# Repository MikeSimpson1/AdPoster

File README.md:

[![Contributors][contributors-shield]][contributors-url]
[![Forks][forks-shield]][forks-url]
[![Stargazers][stars-shield]][stars-url]
[![Issues][issues-shield]][issues-url]
[![LinkedIn][linkedin-shield]][linkedin-url]

<!-- PROJECT LOGO -->
<br />
<div align="center">

  <h3 align="center">Marketplace Ad Poster</h3>

  <p align="center">
    <br />
    <a href="https://github.com/MikeSimpson1/AdPoster"><strong>Explore the docs »</strong></a>
    <br />
    <br />
    <a href="https://github.com/MikeSimpson1/AdPoster">View Demo</a>
    ·
    <a href="https://github.com/MikeSimpson1/AdPoster/issues">Report Bug</a>
    ·
    <a href="https://github.com/MikeSimpson1/AdPoster/issues">Request Feature</a>
  </p>
</div>

<!-- TABLE OF CONTENTS -->
<details>
  <summary>Table of Contents</summary>
  <ol>
    <li>
      <a href="#about-the-project">About The Project</a>
      <ul>
        <li><a href="#built-with">Built With</a></li>
      </ul>
    </li>
  </ol>
</details>

<!-- ABOUT THE PROJECT -->
## About The Project

[![Product Name Screen Shot][product-screenshot]](https://example.com)

Lorem ipsum

<p align="right">(<a href="#readme-top">back to top</a>)</p>

### Built With

* [![Python][Python]][Python-url]
* [![Selenium][Selenium]][Selenium-url]
* [![OpenCV][OpenCV]][OpenCV-url]

<p align="right">(<a href="#readme-top">back to top</a>)</p>

<!-- MARKDOWN LINKS & IMAGES -->
[contributors-shield]: https://img.shields.io/github/contributors/MikeSimpson1/AdPoster.svg?style=for-the-badge
[contributors-url]: https://github.com/MikeSimpson1/AdPoster/graphs/contributors
[forks-shield]: https://img.shields.io/github/forks/MikeSimpson1/AdPoster.svg?style=for-the-badge
[forks-url]: https://github.com/MikeSimpson1/AdPoster/network/members
[stars-shield]: https://img.shields.io/github/stars/MikeSimpson1/AdPoster.svg?style=for-the-badge
[stars-url]: https://github.com/MikeSimpson1/AdPoster/stargazers
[issues-shield]: https://img.shields.io/github/issues/MikeSimpson1/AdPoster.svg?style=for-the-badge
[issues-url]: https://github.com/MikeSimpson1/AdPoster/issues
[license-shield]: https://img.shields.io/github/license/MikeSimpson1/AdPoster.svg?style=for-the-badge
[license-url]: https://github.com/MikeSimpson1/AdPoster/blob/master/LICENSE.txt
[linkedin-shield]: https://img.shields.io/badge/-LinkedIn-black.svg?style=for-the-badge&logo=linkedin&colorB=555
[linkedin-url]: https://linkedin.com/in/mike-simpson-86237419a/
[product-screenshot]: ProductImages/Uncased_device.jpg
[Selenium]: https://img.shields.io/pypi/pyversions/Selenium?logo=Selenium
[Selenium-url]: https://www.selenium.dev/
[Python]: https://img.shields.io/pypi/pyversions/pybadges.svg
[Python-url]: https://www.python.org/
[OpenCV]: https://img.shields.io/pypi/pyversions/Opencv-python?logo=OpenCV
[OpenCV-url]: https://pypi.org/project/opencv-python/

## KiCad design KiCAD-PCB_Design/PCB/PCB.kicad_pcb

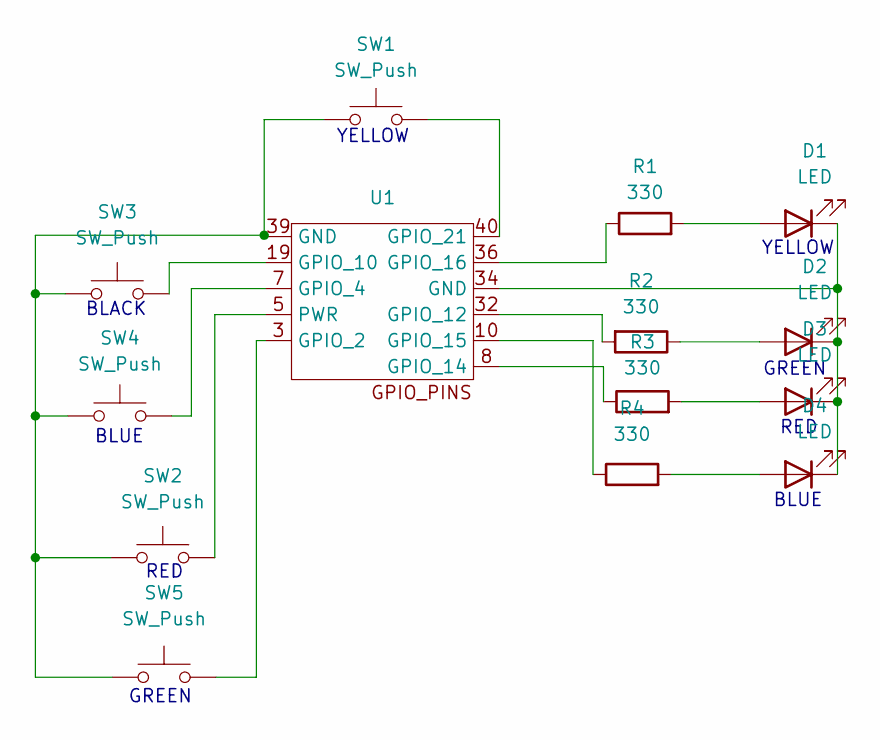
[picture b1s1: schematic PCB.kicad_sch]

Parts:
D1, D2, D3, D4: LED; LED_D5.0mm
R1, R2, R3, R4: 330; R_0201_0603Metric
SW1, SW2, SW3, SW4, SW5: SW_Push; SW_PUSH-12mm
U1: GPIO_PINS_TEST

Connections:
unnamed: D1.2 (A), R1.2
unnamed: D1.1 (K), D2.1 (K), D3.1 (K), D4.1 (K), U1.34 (GND)
unnamed: D2.2 (A), R2.1
unnamed: D3.2 (A), R3.2
unnamed: D4.2 (A), R4.2
unnamed: SW1.1, SW2.1, SW3.1, SW4.1, SW5.1, U1.39 (GND)
unnamed: SW5.2, U1.3 (GPIO_2)
unnamed: SW4.2, U1.7 (GPIO_4)
unnamed: SW3.2, U1.19 (GPIO_10)
unnamed: R2.2, U1.32 (GPIO_12)
unnamed: R3.1, U1.8 (GPIO_14)
unnamed: R4.1, U1.10 (GPIO_15)
unnamed: R1.1, U1.36 (GPIO_16)
unnamed: SW1.2, U1.40 (GPIO_21)
unnamed: SW2.2, U1.5 (PWR)

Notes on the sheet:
YELLOW
RED
BLUE
BLACK
GREEN

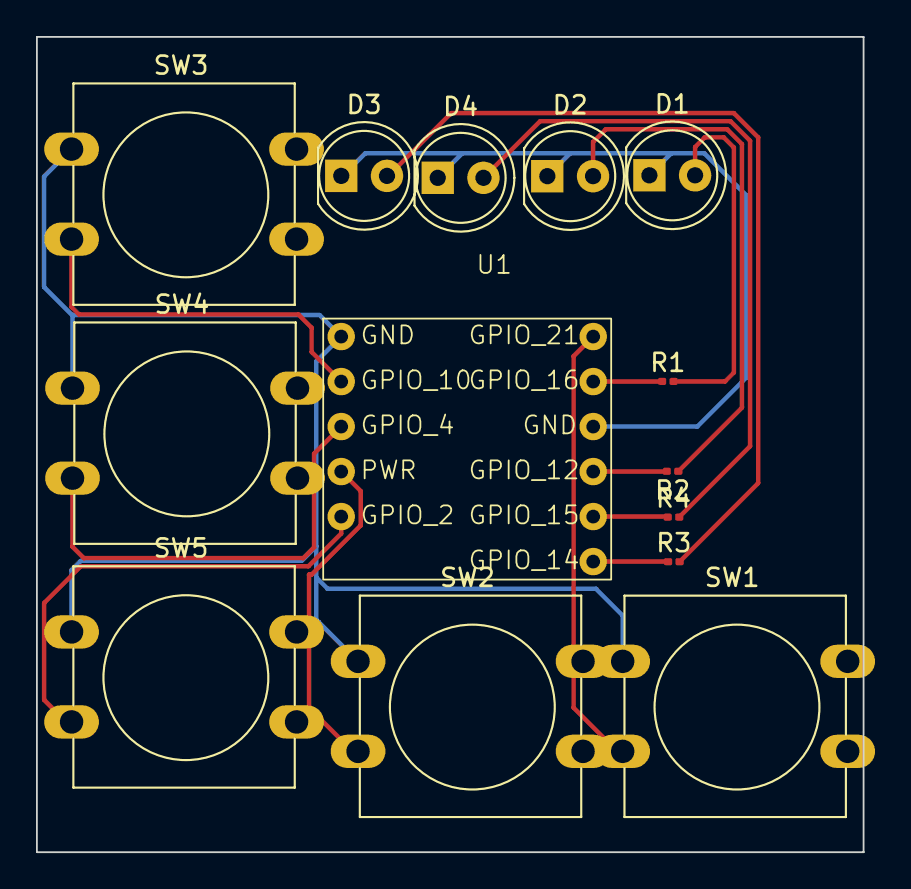
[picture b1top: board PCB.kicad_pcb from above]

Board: 2 copper layers, 45.9 x 45.3 mm, 14 parts (0 on the bottom side), 15 nets.

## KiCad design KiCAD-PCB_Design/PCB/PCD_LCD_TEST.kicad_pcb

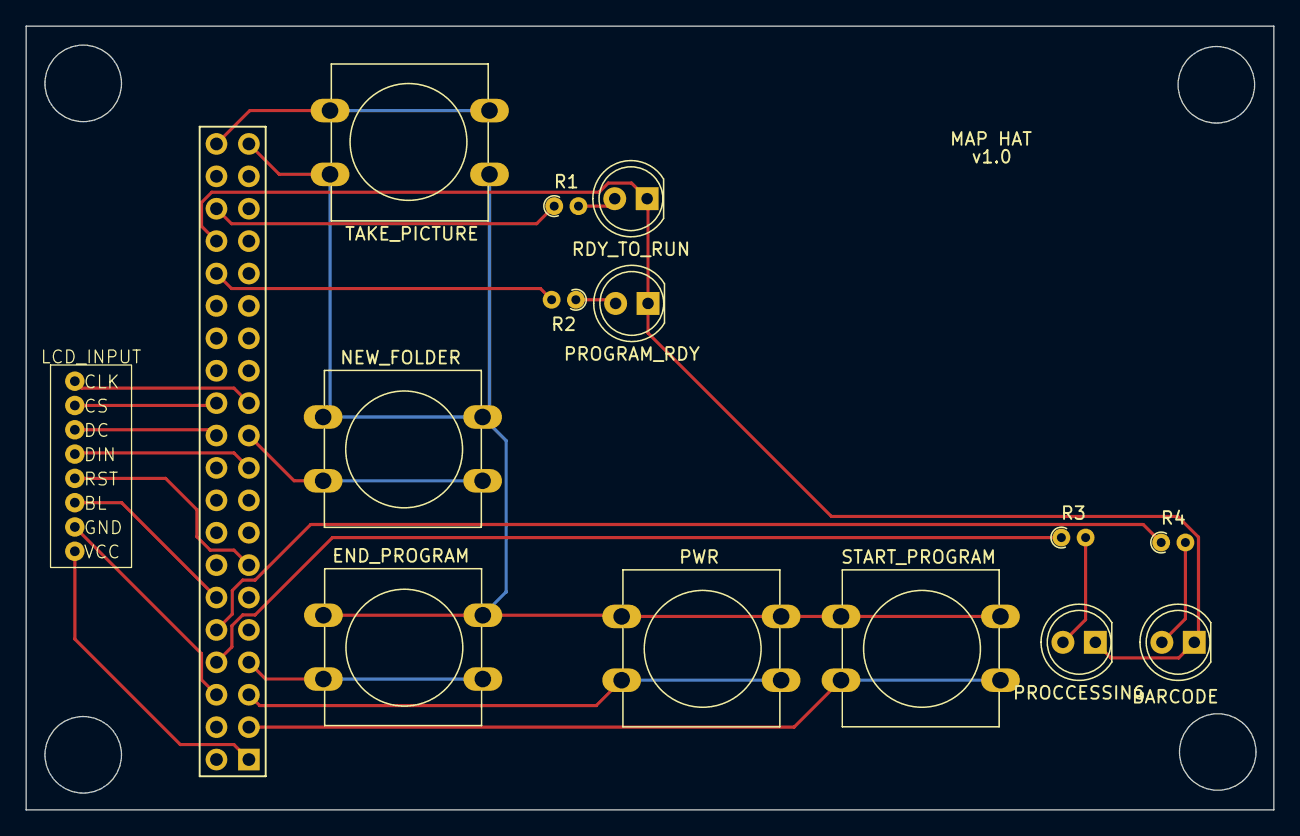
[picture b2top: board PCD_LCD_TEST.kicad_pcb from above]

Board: 2 copper layers, 97.8 x 61.4 mm, 15 parts (1 on the bottom side), 23 nets.

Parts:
BARCODE: LED; LED_D5.0mm
END_PROGRAM: SW_Push; SW_PUSH-12mm
LCD_INPUT: LCD
NEW_FOLDER: SW_Push; SW_PUSH-12mm
PROCCESSING: LED; LED_D5.0mm
PROGRAM_RDY: LED; LED_D5.0mm
PWR: SW_Push; SW_PUSH-12mm
R1, R2, R3, R4: 330; R_Axial_DIN0204_L3.6mm_D1.6mm_P1.90mm_Vertical
RDY_TO_RUN: RDY_TO_RUN; LED_D5.0mm
START_PROGRAM: SW_Push; SW_PUSH-12mm
TAKE_PICTURE: TAKE_PICTURE; SW_PUSH-12mm
U1: Raspberry_Pi_Socketed_THT_FaceDown_MountingHoles

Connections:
unnamed: R1.2, RDY_TO_RUN.2 (A)
unnamed: BARCODE.1 (K), PROCCESSING.1 (K), PROGRAM_RDY.1 (K), RDY_TO_RUN.1 (K), U1.34
unnamed: PROGRAM_RDY.2 (A), R2.1
unnamed: PROCCESSING.2 (A), R3.2
unnamed: BARCODE.2 (A), R4.2
unnamed: R1.1, U1.36
unnamed: R2.2, U1.32
unnamed: R3.1, U1.8
unnamed: R4.1, U1.10
unnamed: END_PROGRAM.1, NEW_FOLDER.1, PWR.1, START_PROGRAM.1, TAKE_PICTURE.1, U1.39
unnamed: TAKE_PICTURE.2, U1.40
unnamed: PWR.2, U1.5
unnamed: NEW_FOLDER.2, U1.21
unnamed: END_PROGRAM.2, U1.7
unnamed: START_PROGRAM.2, U1.3
unnamed: LCD_INPUT.8 (BL), U1.12
unnamed: LCD_INPUT.4 (CLK), U1.23
unnamed: LCD_INPUT.5 (CS), U1.24
unnamed: LCD_INPUT.6 (DC), U1.22
unnamed: LCD_INPUT.3 (DIN), U1.19
unnamed: LCD_INPUT.2 (GND), U1.6
unnamed: LCD_INPUT.7 (RST), U1.13
unnamed: LCD_INPUT.1 (VCC), U1.1

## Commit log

2023-07-15 First real commit
2023-07-15 Added rPi code
2023-07-30 Reworked directories and fixed ssh issue
2023-07-30 Removed unused files
2023-07-30 Removed images
2023-07-30 Further changes
2023-08-09 Added barcode reader
2023-08-09 Generate meta file from barcode
2023-08-09 Further improvements
2023-08-09 Added barcode detection to main script
2023-08-09 added blue LED for barcode detection
2023-08-10 Read file and find title and author
2023-08-17 PCB and Case starter designs
2023-08-17 Renamed files
2023-08-17 Renamed vars in cam application
2023-08-20 Introduced LCD to project
2023-08-26 Latest PCB design, GPIO changes
2023-09-24 Added google books API wrapper
2023-09-30 Fixed GPIO connections
2023-10-16 Make everything up to date.
2023-10-16 Test
2023-10-16 fixed merge conflicts
2023-10-29 Finished the 3D case design!
2023-11-12 Added price lookup
2023-11-12 Updated gitignore
2023-11-12 Removed all __pycache__ bloat
2023-11-12 Integrated price lookup into metadata generator
2023-11-18 Started improving the readme
2023-11-18 Update python sheild
